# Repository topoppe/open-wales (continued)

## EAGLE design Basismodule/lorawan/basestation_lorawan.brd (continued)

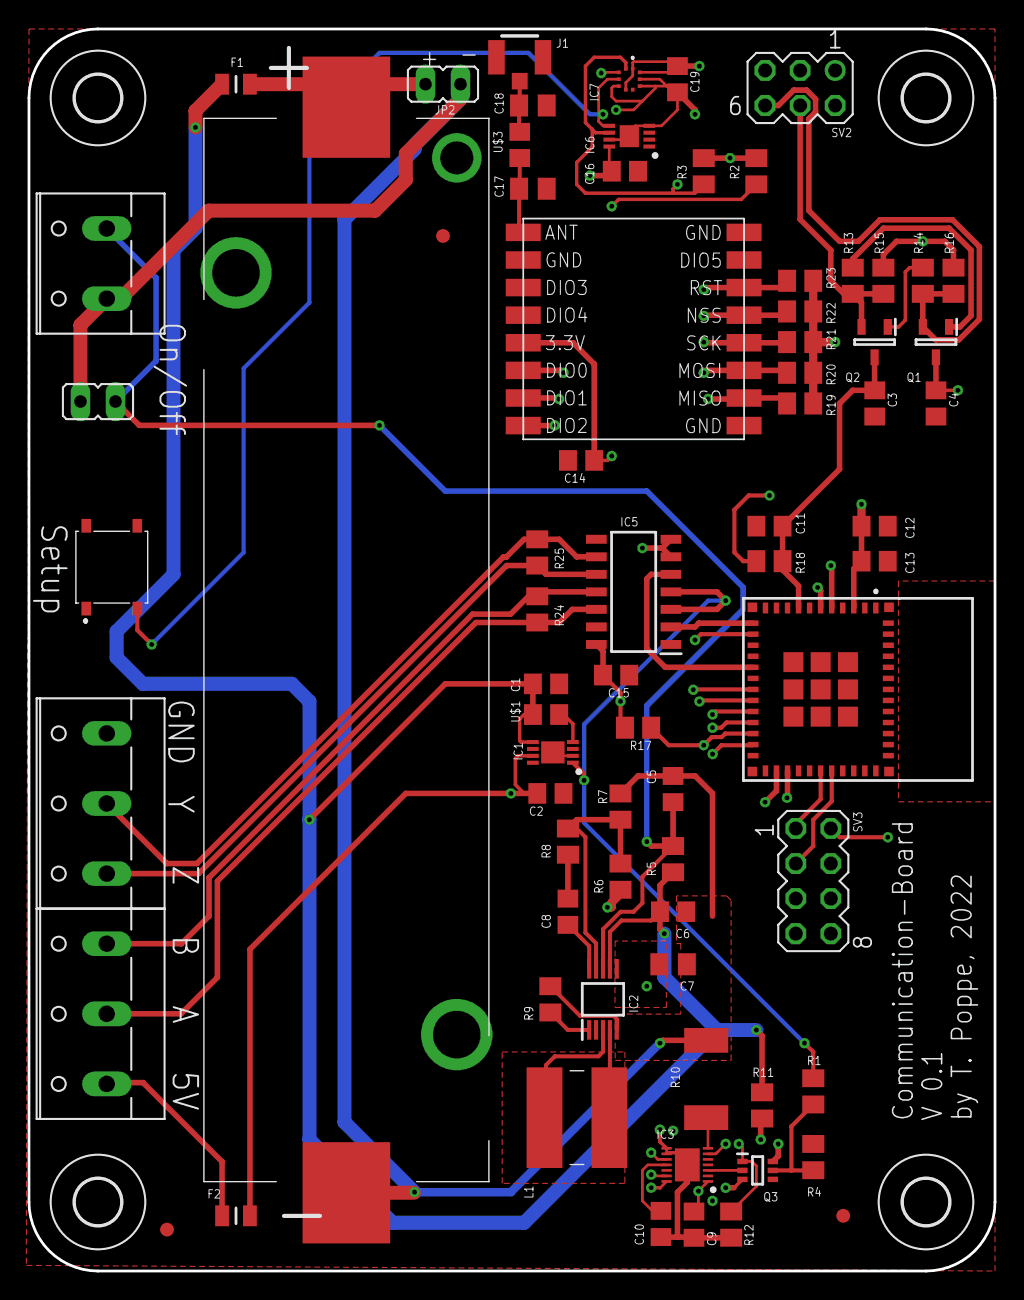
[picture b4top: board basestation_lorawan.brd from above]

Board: 4 copper layers, 70.0 x 90.0 mm, 77 parts (0 on the bottom side), 47 nets.

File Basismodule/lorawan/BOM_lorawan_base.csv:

Qty;Value;Parts;MOUSER_PART_NUMBER
4;10uF/6.3V(20%);C1, C2, C6, C13;963-JMK212BJ106MG-T
1; 0.47uF/16V(5%);C10;77-VJ0805Y474JXJTBC 
1;1uF/10V(10%);C11;710-885012207078 
2; 0.1uF/50V(10%) DNP;C3, C4; 80-C0805C104K5RACLR
7; 0.1uF/50V(10%);C5, C9, C12, C14, C15, C16, C19; 80-C0805C104K5RACLR
1;22uF/6.3V(20%);C7;710-885012107005
1;1.5nF/50V(5%);C8;80-C0805C152J5GAC
2;0ZCK0050FF2E;F1, F2;530-0ZCK0050FF2E 
1;DIO6605BFN8;IC1;453-DIO6605BFN8
1;LTC3440EMS#TRPBF;IC2;584-LTC3440EMS#TRPBF
1;MAX17261METD+;IC3;700-MAX17261METD+
1;ESP32-C3-MINI-1-N4;IC4;356-ESP32-C3-MINI1N4
1;SP3076EEN-L;IC5;701-SP3076EEN-L
1;AT24C16D-MAHM-E;IC6;579-AT24C16D-MAHM-E
1;BMP384;IC7;262-BMP384
1;RECE-20279-001E-01;J1;960-RECE20279001E01 
1;SRR6038-100Y;L1;652-SRR6038-100Y
2;S8050G;Q1, Q2;750-SS8050-G
1;BSD235NH6327XTSA1;Q3;726-BSD235NH6327XTS
1;180(1%);R1;652-CR0805FX-1800ELF
1;100mOhm, 3W, 1%;R10;652-CRA2512FZR100ELF 
1;300k(1%);R11;667-ERJ-P06F3003V
2;22k(1%);R15, R16;603-RC0805FR-1322KL
2;4k7(1%);R2, R3;603-RC0805FR-104K7L
2;100(1%);R24, R25;603-RC0805FR-13100RL
9;10k(1%);R4, R13, R14, R18, R19, R20, R21, R22, R23;71-CRCW080510K0FKEAC
1;1M(1%);R5;603-RC0805FR-131ML
1;340k(1%);R6;RC0805FR-13330KL
2;200k(1%);R7, R12;603-RC0805FR-13200KL
1;15k(1%);R8;652-CR0805FX-1502ELF
1;60.4k(1%);R9;603-RC0805FR-0760K4L
1;PTS526_SK15_SMTR2_LFS;S1;611-PTS526SK15SMR2L
1;PinHeader 11 Pos;SV2;517-2312-6111TG
1;4.7uH;U$1;963-MBMK2520T4R7M
1;RFM95W;U$2;223-RFM95W-915S2
1;1042P;U1;534-1042P
4;WAGO SREW CLAMP;X1;710-691216710002
